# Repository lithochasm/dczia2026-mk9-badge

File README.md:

```
___  ____     _____  ______           _            
|  \/  | |   |  _  | | ___ \         | |           
| .  . | | __| |_| | | |_/ / __ _  __| | __ _  ___ 
| |\/| | |/ /\____ | | ___ \/ _` |/ _` |/ _` |/ _ \
| |  | |   < .___/ / | |_/ / (_| | (_| | (_| |  __/
\_|  |_/_|\_\\____/  \____/ \__,_|\__,_|\__, |\___|
                                         __/ |     
                                        |___/      
-------------------------------------------------
D C Z I A  ----------  2 0 2 6
```

DCZia Presents: The MK9 Badge

It blinks. It types. You can wear it around your neck and then set it on your desk and actually use it\*.

\* _Desk productivity not guaranteed. DCZia assumes no responsibility for keys accidentally sent during badge parties. Consult your keyboard layer documentation before operating heavy machinery._

---

## About

The **MK9** is a fully functional **3×3 mechanical macropad badge**. Nine real mechanical switches, per-key RGB lighting, ambient underglow, an accelerometer that actually does something interesting, SAO support, and MicroPython firmware — all in a package sized to hang around your neck at DEF CON and survive the week.

---

## Specs

**Keys**
- 9× mechanical switches in a 3×3 grid — standard MX footprint, swap keycaps as you please
- Ships with translucent blue keycaps
- USB HID numpad when plugged into a computer

**Lighting**
- 9× WS2812B per-key RGB LEDs — one under each switch
- 6× SK6812 side-firing LEDs — edge-mounted for ambient underglow out the sides

**Brains & Sensors**
- RP2040 microcontroller
- Accelerometer — light stays pooled at physical down as a hanging badge rotates
- 2× SAO connectors (standard 6-pin, I2C + 2 GPIO each) — expand with the badge add-on ecosystem

**Power & I/O**
- USB-C — power and data
- 3× AAA battery pack — run it untethered
- Power switch for battery mode
- Reset button + BOOTSEL button for easy firmware flashing

**Firmware**
- Native MicroPython firmware with bundled USB HID support
- QMK-compatible hardware — reflash and run it as a full QMK macropad

---

## What It Does Out of the Box

On boot: a smoothly fading rainbow flows across all keys and backlights, then
cross-fades into the active theme.

Once running:
- Nine spatial color themes animate all 15 LEDs — one theme for each key
- Pressing a key makes a white-hot impact and a colour ripple that expands across the whole board
- Long-press a key to select its theme; rotation keeps its light pooled at physical down
- Plug into a computer and it shows up as a numpad (7–9 / 4–6 / 1–3 layout)

---

## Repository

```
mk9-badge/
├── buildguide.md — badge assembly, flashing, and troubleshooting
├── hardware/   — KiCad design files, BOM, fabrication outputs
└── software/   — MicroPython firmware
```

- [Build Guide →](buildguide.md) — assembly, battery installation, flashing, and troubleshooting
- [Hardware →](hardware/README.md) — schematics, PCB layout, drill files, BOM
- [Software →](software/README.md) — firmware architecture, pinout, library requirements, flashing instructions

**Fabrication outputs**:
- [PCB layer plot](hardware/output/mk9-badge.pdf)
- [PTH drill map](hardware/output/mk9-badge-PTH-drl_map.pdf)
- [NPTH drill map](hardware/output/mk9-badge-NPTH-drl_map.pdf)

---

## Programming / Updating

The badge runs [MicroPython](https://micropython.org). To install or update it:

1. Hold **BOOTSEL** while plugging the badge into your computer — it mounts as `RPI-RP2`.
2. Drag [`firmware/RPI_PICO-20260406-v1.28.0.uf2`](firmware/RPI_PICO-20260406-v1.28.0.uf2)
   onto the drive.
3. Use Thonny or `mpremote` to upload the `software/*.py` files to `/` and
   `software/lib/` to `/lib/` on the badge.

Full commands and the recommended firmware version are in the
[software flashing guide](software/README.md#install-on-the-badge).

Want to run QMK instead? The hardware is fully compatible; QMK setup instructions will be posted separately.

**Recommended tool:** [Thonny](https://thonny.org), which can edit and upload
files directly through the MicroPython serial connection.

---

## Open Source

DCZia is committed to open source hardware and software. All design files and firmware are publicly available.

- **Live CAD (OnShape):** [View the design](https://cad.onshape.com/documents/36884624fbe35c16a5af61a7/w/233227193d278274727a44c3/e/ea987b4b53c4648fa3dc84b6)

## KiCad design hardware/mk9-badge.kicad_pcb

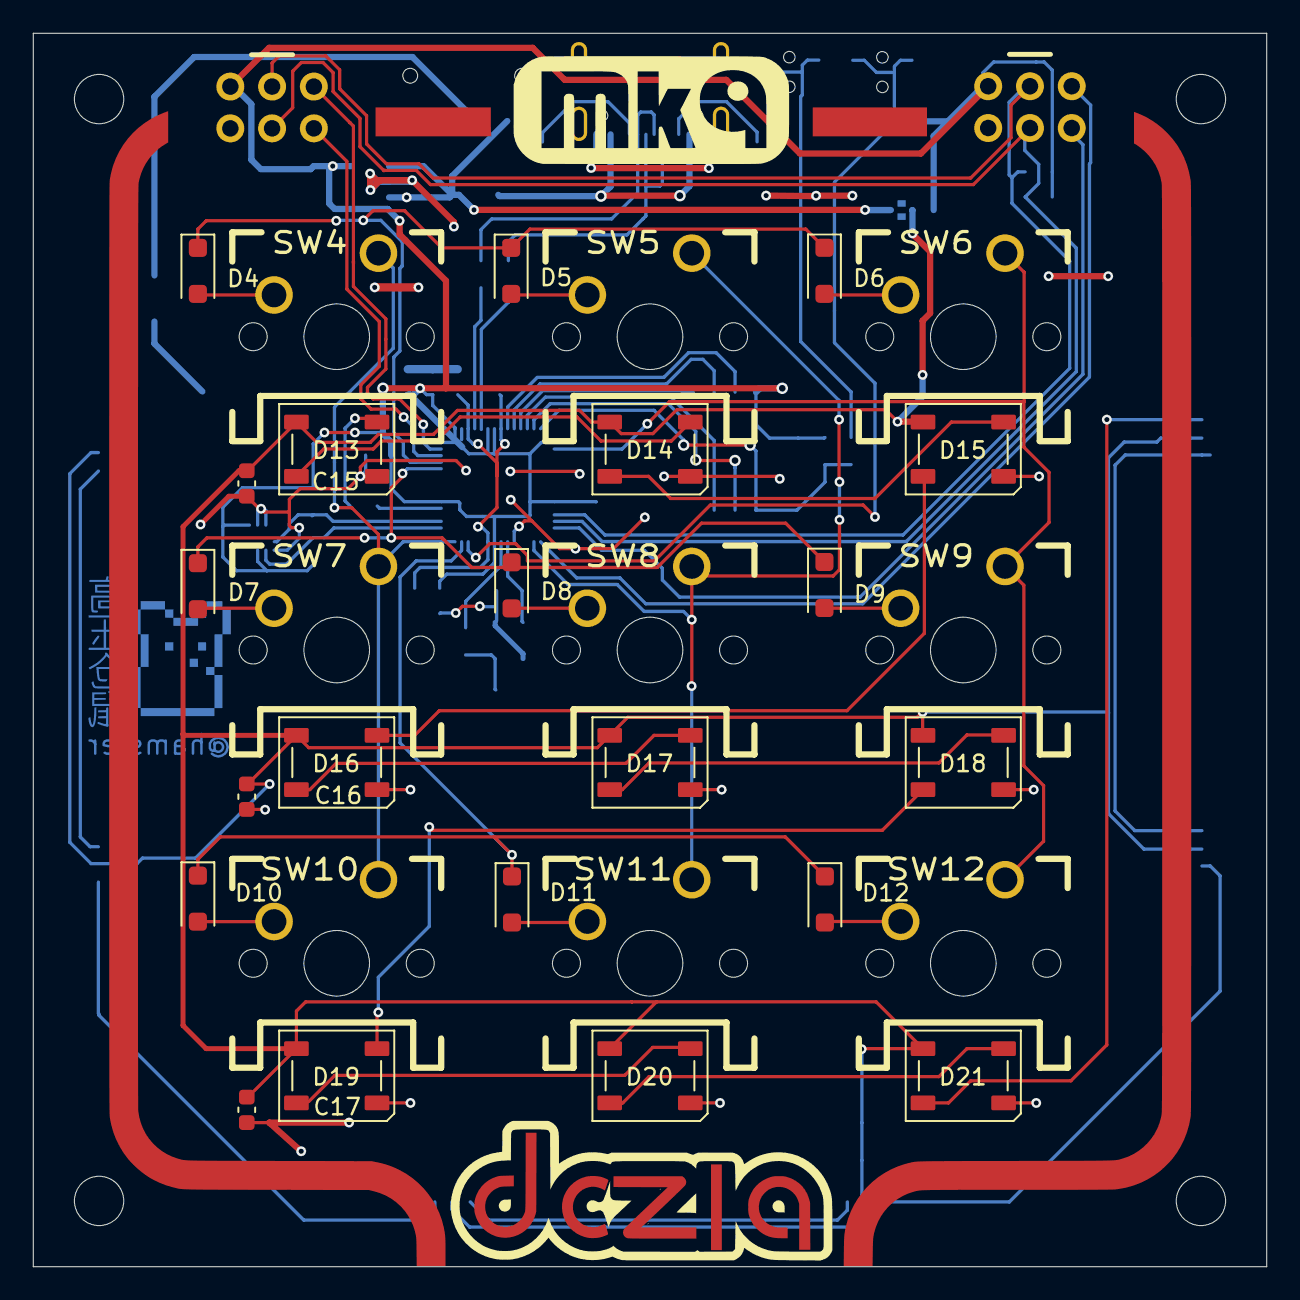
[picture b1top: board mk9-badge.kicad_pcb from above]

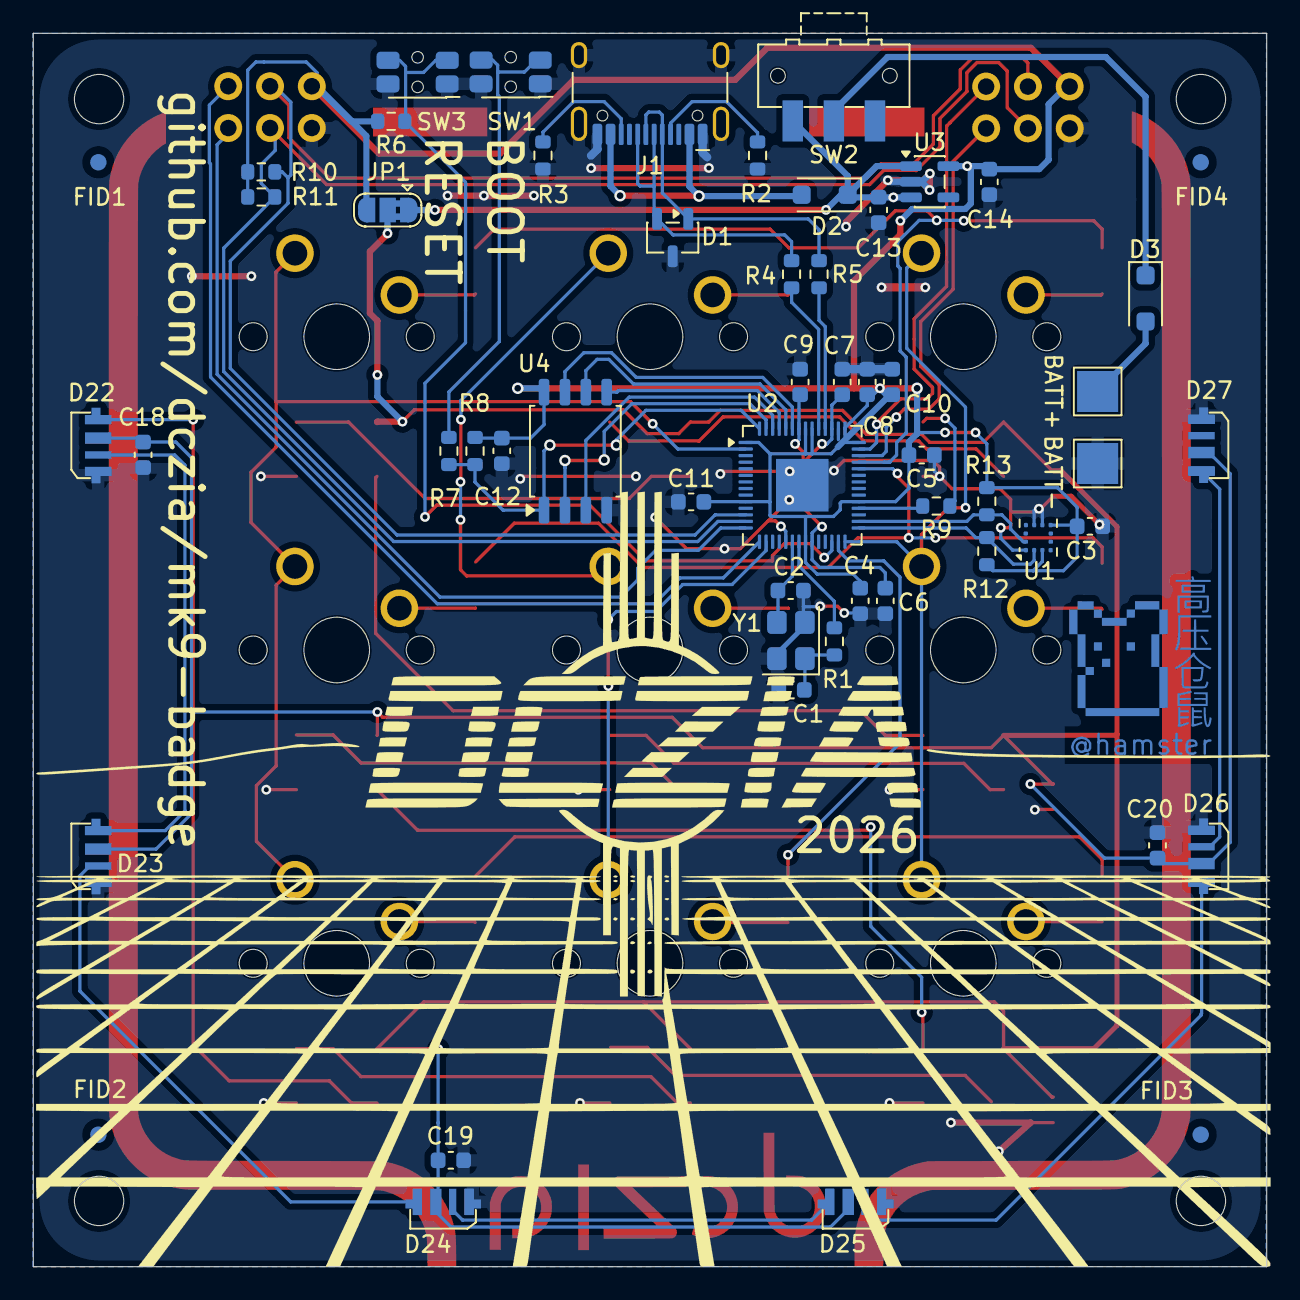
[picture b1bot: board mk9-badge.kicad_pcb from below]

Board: 2 copper layers, 75.0 x 75.0 mm, 87 parts (55 on the bottom side), 64 nets.

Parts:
C1, C2: 15pF; C_0603_1608Metric
C3, C5, C6, C8, C9, C10, C11, C12, C15, C16, C17, C18, C19, C20: 0.1uF; C_0603_1608Metric
C4, C7, C13, C14: 1uF; C_0603_1608Metric
D1: SP0503BAHT; SOT-23-3
D2, D3, D4, D5, D6, D7, D8, D9, D10, D11, D12: D_Schottky; D_SOD-123F
D13, D14, D15, D16, D17, D18, D19, D20, D21: WS2812B; LED_WS2812B_PLCC4_5.0x5.0mm_P3.2mm_Update
D22, D23, D24, D25, D26, D27: SK6812; LED_SK6812_4020
FID1, FID2, FID3, FID4: Fiducial; Fiducial_1mm_Mask2mm
J1: USB-C; USB_C_Receptacle_HCTL_HC-TYPE-C-16P-01A
JP1: LED Power Select; SolderJumper-3_P1.3mm_Bridged2Bar12_RoundedPad1.0x1.5mm
R1, R7: 1k; R_0603_1608Metric
R2, R3: 5.1k; R_0603_1608Metric
R4, R5: 27R; R_0603_1608Metric
R6, R8: 10k; R_0603_1608Metric
R9: 10R; R_0603_1608Metric
R10, R11, R12, R13: 4.7k; R_0603_1608Metric
SW1: Boot Select; SW_SPST_EVQP7C
SW2: SW_SPDT; SW_SPDT_CK-JS102011SAQN
SW3: Reset; SW_SPST_EVQP7C
SW4, SW5, SW6, SW7, SW8, SW9, SW10, SW11, SW12: SW_Push; CHERRY_SMDLED_100H
TP5: BATT+; TestPoint_Pad_2.5x2.5mm
TP6: BATT-; TestPoint_Pad_2.5x2.5mm
U1: GSDA213; Kionix_LGA-12_2x2mm_P0.5mm_LayoutBorder2x4y
U2: RP2040; QFN-56-1EP_7x7mm_P0.4mm_EP3.2x3.2mm
U3: NCP115ASN330T2G; SOT-23-5
U4: W25Q128JVSIM; SOIC-8_5.3x5.3mm_P1.27mm
X1, X2: Badgelife_sao_connector_v169bis; Badgelife-Shitty-v1.69bis
Y1: ABM8-272-T3; Crystal_SMD_Abracon_ABM8G-4Pin_3.2x2.5mm

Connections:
+3.3V: C3.2, C4.2, C5.2, C8.2, C10.2, C11.2, C12.2, C14.2, JP1.3 (B), R6.2, R8.2, R10.2, R11.2, R12.2, R13.2, U1.3 (VDD_IO), U1.7 (VDD), U2.1 (IOVDD), U2.10 (IOVDD), U2.22 (IOVDD), U2.33 (IOVDD), U2.42 (IOVDD), U2.43 (ADC_AVDD), U2.44 (VREG_IN), U2.48 (USB_VDD), U2.49 (IOVDD), U3.5 (OUT), U4.8 (VCC), X1.1 (VCC), X2.1 (VCC)
C0: SW4.1, SW7.1, SW10.1, U2.28 (GPIO17)
C1: SW5.1, SW8.1, SW11.1, U2.16 (GPIO13)
C2: SW6.1, SW9.1, SW12.1, U2.2 (GPIO0)
CLK: U2.52 (QSPI_SCLK), U4.6 (CLK)
DS0: U2.53 (QSPI_SD0), U4.5 (DI(IO0))
DS1: U2.55 (QSPI_SD1), U4.2 (DO(IO1))
DS2: U2.54 (QSPI_SD2), U4.3 (IO2)
DS3: U2.51 (QSPI_SD3), U4.7 (IO3)
GND: C1.1, C2.1, C3.1, C4.1, C5.1, C6.1, C7.1, C8.1, C9.1, C10.1, C11.1, C12.1, C13.1, C14.1, C15.2, C16.2, C17.2, C18.2, C19.2, C20.2, D1.3 (A), D13.3 (VSS), D14.3 (VSS), D15.3 (VSS), D16.3 (VSS), D17.3 (VSS), D18.3 (VSS), D19.3 (VSS), D20.3 (VSS), D21.3 (VSS), D22.4 (VSS), D23.4 (VSS), D24.4 (VSS), D25.4 (VSS), D26.4 (VSS), D27.4 (VSS), J1.A1 (GND), J1.A12 (GND), J1.B1 (GND), J1.B12 (GND), J1.SH (SHIELD), R2.2, R3.2, SW1.1, SW3.1, TP6.1 (1_1), U1.1 (SA0), U1.8 (GND_IO), U1.9 (GND), U2.19 (TESTEN), U2.57 (GND), U3.2 (GND), U4.4 (GND), X1.2 (GND), X2.2 (GND), Y1.2, Y1.4
unnamed: C1.2, R1.1, Y1.1
unnamed: D1.1 (K), J1.A7 (D-), J1.B7 (D-), R4.2
unnamed: D1.2 (K), J1.A6 (D+), J1.B6 (D+), R5.1
unnamed: D3.2 (A), TP5.1 (1_1)
unnamed: D3.1 (K), SW2.2 (B)
unnamed: D4.2 (A), SW4.2
unnamed: D5.2 (A), SW5.2
unnamed: D6.2 (A), SW6.2
unnamed: D7.2 (A), SW7.2
unnamed: D8.2 (A), SW8.2
unnamed: D9.2 (A), SW9.2
unnamed: D10.2 (A), SW10.2
unnamed: D11.2 (A), SW11.2
unnamed: D12.2 (A), SW12.2
unnamed: D13.4 (DIN), R9.1
unnamed: D13.2 (DOUT), D14.4 (DIN)
unnamed: D14.2 (DOUT), D15.4 (DIN)
unnamed: D15.2 (DOUT), D16.4 (DIN)
unnamed: D16.2 (DOUT), D17.4 (DIN)
unnamed: D17.2 (DOUT), D18.4 (DIN)
unnamed: D18.2 (DOUT), D19.4 (DIN)
unnamed: D19.2 (DOUT), D20.4 (DIN)
unnamed: D20.2 (DOUT), D21.4 (DIN)
unnamed: D22.3 (DOUT), D23.1 (DIN)
unnamed: D23.3 (DOUT), D24.1 (DIN)
unnamed: D24.3 (DOUT), D25.1 (DIN)
unnamed: D25.3 (DOUT), D26.1 (DIN)
unnamed: D26.3 (DOUT), D27.1 (DIN)
unnamed: J1.A5 (CC1), R2.1
unnamed: J1.B5 (CC2), R3.1
unnamed: R7.1, SW1.2
unnamed: R6.1, SW3.2, U2.26 (RUN)
unnamed: C6.2, C7.2, C9.2, U2.23 (DVDD), U2.45 (VREG_VOUT), U2.50 (DVDD)
R0: D4.1 (K), D5.1 (K), D6.1 (K), U2.39 (GPIO27_ADC1)
R1: D7.1 (K), D8.1 (K), D9.1 (K), U2.38 (GPIO26_ADC0)
R2: D10.1 (K), D11.1 (K), D12.1 (K), U2.27 (GPIO16)
RGB: R9.2, U2.32 (GPIO21)
SAO1_1: U2.41 (GPIO29_ADC3), X1.5 (GPIO1)
SAO1_2: U2.40 (GPIO28_ADC2), X1.6 (GPIO2)
SAO2_1: U2.15 (GPIO12), X2.5 (GPIO1)
SAO2_2: U2.14 (GPIO11), X2.6 (GPIO2)
SCL0: R11.1, U2.13 (GPIO10), X1.4 (SCL), X2.4 (SCL)
SCL1: R13.1, U1.12 (SCL), U2.30 (GPIO19)
SDA0: R10.1, U2.12 (GPIO9), X1.3 (SDA), X2.3 (SDA)
SDA1: R12.1, U1.2 (SDA), U2.29 (GPIO18)
SIDE_LEDS: D21.2 (DOUT), D22.1 (DIN)
SS: R7.2, R8.1, U2.56 (QSPI_SS), U4.1 (~CS)
USB_N: R4.1, U2.46 (USB_DM)
USB_P: R5.2, U2.47 (USB_DP)
VBUS: D2.2 (A), J1.A4 (VBUS), J1.A9 (VBUS), J1.B4 (VBUS), J1.B9 (VBUS)
VCC: C13.2, D2.1 (K), JP1.1 (A), SW2.3 (C), U3.1 (IN), U3.3 (EN)
VLED: C15.1, C16.1, C17.1, C18.1, C19.1, C20.1, D13.1 (VDD), D14.1 (VDD), D15.1 (VDD), D16.1 (VDD), D17.1 (VDD), D18.1 (VDD), D19.1 (VDD), D20.1 (VDD), D21.1 (VDD), D22.2 (VDD), D23.2 (VDD), D24.2 (VDD), D25.2 (VDD), D26.2 (VDD), D27.2 (VDD), JP1.2 (C)
XTAL_IN: C2.2, U2.20 (XIN), Y1.3
XTAL_OUT: R1.2, U2.21 (XOUT)

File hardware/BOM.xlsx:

Reference | Feeder | Value | Footprint | Part Number | Distributor | Distributor Part | Datasheet | Qty | Cost Each | Qty Ordered | QOH | Notes
C3,C5,C6,C8-C12,C15-C20 |  | 0.1uF | 0603 |  |  |  | ~ | 14 | 4.0000000000000001E-3 | 0 | 2500
C4,C7,C13,C14 |  | 1uF | 0603 |  |  |  | ~ | 4 | 4.0000000000000001E-3 | 0 | 3500
C1,C2 |  | 15pF | 0603 |  |  |  | ~ | 2 | 4.0000000000000001E-3 | 0 | 3500
D2-12 |  | D_Schottky | SOD-123 |  | Digikey | 3757-SS0540_R1_00001DKR-ND | https://www.panjit.com.tw/upload/datasheet/SS0520_SERIES.pdf | 2 | 0.11 | 0 | 2500
D13-21 |  | WS2812B | LED_SMD:LED_WS2812B_PLCC4_5.0x5.0mm_P3.2mm |  | Aliexpress | https://www.aliexpress.us/item/2251832628463811.html?spm=a2g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 | https://cdn-shop.adafruit.com/datasheets/WS2812B.pdf | 9 | 7.0000000000000007E-2 | 0 | 2000
D22-27 |  | SK6812 |  |  | Aliexpress |  |  | 6 | 0.1 | 1000 | 0
D1 |  | TVS |  | SP0502BAHTG | Mouser | 576-SP0502BAHTG | https://www.littelfuse.com/assetdocs/tvs-diode-array-spasp05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 | 0 | 0.38300000000000001 |  |  | Optional stuffing
J1 |  | USB-C | Connector_USB:USB_C_Receptacle_HCTL_HC-TYPE-C-16P-01A |  | Aliexpress | https://www.aliexpress.us/item/3256805324706422.html?spm=a2g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 | https://www.lcsc.com/datasheet/lcsc_datasheet_2211161000_HCT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 | 1 | 0.19 | 150 | 100
R1,R7 |  | 1k | 0603 |  |  |  | ~ | 2 | 1E-3 | 0 | 4500
R6,R8 |  | 10k | 0603 |  |  |  | ~ | 2 | 1E-3 | 0 | 4500
R2,R3 |  | 5.1k | 0603 |  |  |  | ~ | 2 | 1E-3 | 0 | 4500
R4,R5 |  | 27R | 0603 |  |  |  | ~ | 2 | 1E-3 | 0 | 4500
R9 |  | 10R | 0603 |  |  |  | ~ | 1 | 1E-3 | 0 | 4500
R10,R11 |  | 4.7k | 0603 |  |  |  |  | 2 | 1E-3 | 5000 | 0
S1,S3 |  | SPST Push w/boss | Button_Switch_SMD:SW_SPST_EVQP7C | EVQ-P7C01P | Digikey | P16765CT-ND | https://api.pim.na.industrial.panasonic.com/file_stream/main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 | 2 | 0.20204 | 300 | 0
S2 |  | SW_SPDT | lib_fp:SW_SPDT_CK-JS102011SAQN | JS102011SAQN | Digikey | 401-1999-1-ND | https://ckswitches.com/media/1422/js.pdf | 1 | 0.60319999999999996 | 150 | 0
S4-12 |  | CherryMX Blue |  |  | Aliexpress |  |  | 9 | 0.1 | 1000 | 0
U3 |  | NCP115ASN330T2G | Package_TO_SOT_SMD:SOT-23-5 | NCP115ASN330T2G | Digikey | NCP115ASN330T2G | https://www.onsemi.com/pdf/datasheet/ncp115-d.pdf | 1 | 6.7699999999999996E-2 | 0 | 2500
U2 |  | RP2040 | Package_DFN_QFN:QFN-56-1EP_7x7mm_P0.4mm_EP3.2x3.2mm | SC0914(7) | Mouser | 358-SC09147 | https://datasheets.raspberrypi.com/rp2040/rp2040-datasheet.pdf | 1 | 0.8 | 0 | 1000
U4 |  | W25Q128JVSIM |  |  | Digikey | W25Q128JVSIM-ND | https://www.winbond.com/resource-files/W25Q128JV%20RevI%2008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 | 1 | 2.5155599999999998 | 133 | 0
U1 |  | GSDA213 | Kionix_LGA-12_2x2mm_P0.5mm_LayoutBorder2x4y | GSDA213 | Digikey | 4786-GSDA213TR-ND | https://goodarksemi.com/docs/datasheets/mems/GSDA213_SDS.pdf | 1 | 0.65949999999999998 | 150 | 0
X1,X2 |  | Badgelife_sao_connector_v169bis | lib_fp:Badgelife-Shitty-v1.69bis | VIRTUAL |  |  |  | 2
Y1 |  | Crystal | Crystal:Crystal_SMD_3225-4Pin_3.2x2.5mm | ABM8-272-T3 | Digikey | 535-ABM8-272-T3DKR-ND | https://abracon.com/datasheets/ABM8-272-T3.pdf | 1 | 0.40849999999999997 | 150 | 0
 |  | Key caps |  |  |  |  |  | 9 | 0.19 | 1500
` |  | Battery boxes |  |  |  |  |  | 1 |  | 125
 |  | PCB |  |  |  |  |  | 1 |  | 200
 |  | Batteries |  |  | Amazon |  |  | 3 | 0.15 | 300
 |  | Badge Run, units | 120

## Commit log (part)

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2026-06-26 Porting in Zippy badge firmware Adding in testing firmware Adding a README
2026-06-26 It's 2026, hamster.
2026-06-26 README updates
